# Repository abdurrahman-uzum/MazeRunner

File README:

A maze solving mini robot project conducted under Dokuz Eylül University Robot Topluluğu MazeRunner subgroup.

Project is uncomplete and discontinued.

Works present in this repository are my own works.

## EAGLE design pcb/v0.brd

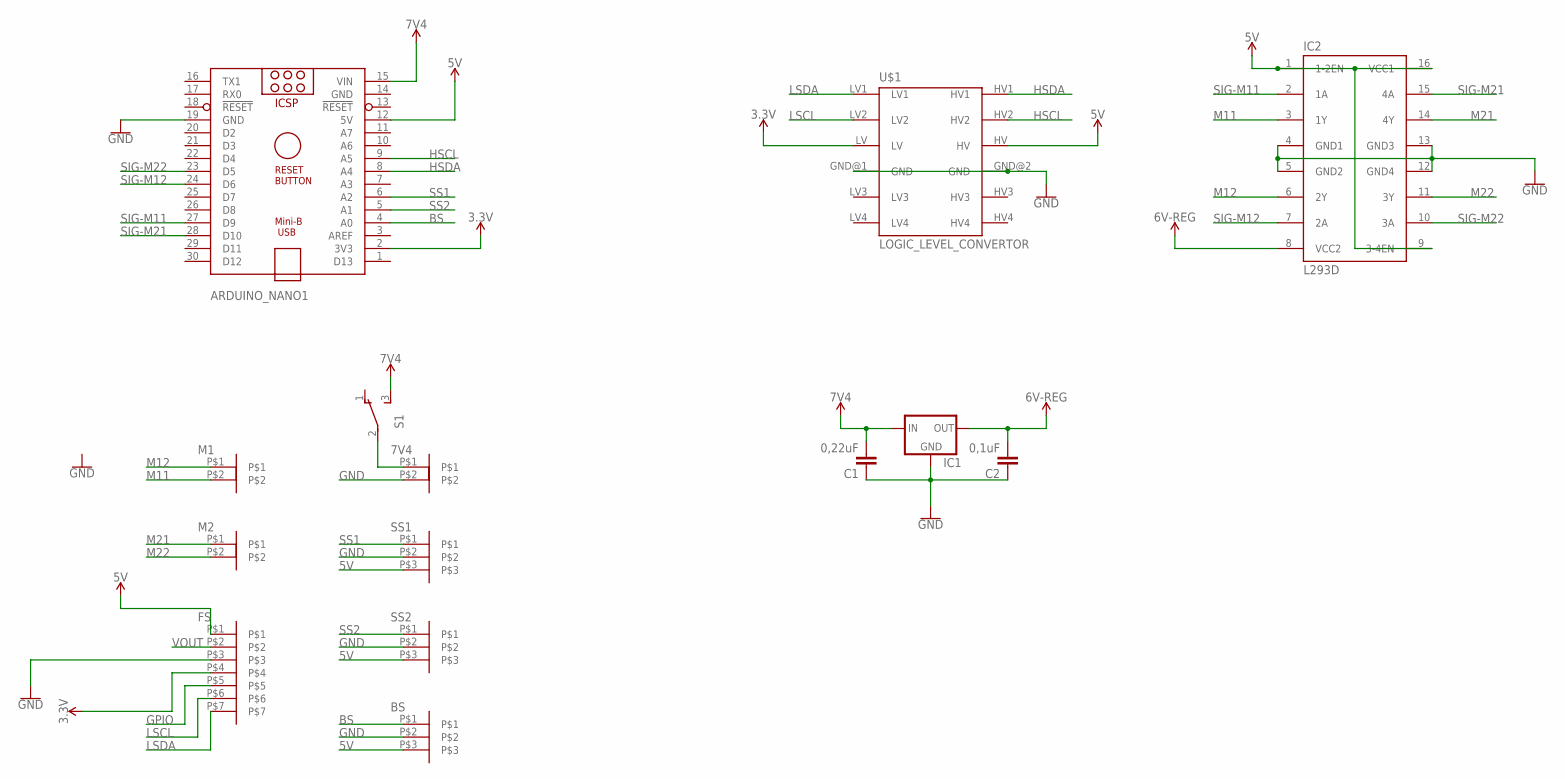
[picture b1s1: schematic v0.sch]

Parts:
7V4: 2MM_JST_2
ARDUINO_NANO1: ARDUINO_NANO
BS: 2MM_JST_3
C1: 0,22uF; C050-025X075
C2: 0,1uF; C050-025X075
FS: 2MM_JST_7
IC1: 78XXL
IC2: L293D; DIL16
M1, M2: 2MM_JST_2
S1: TL36PO; TL3XPO
SS1, SS2: 2MM_JST_3
U$1: LOGIC_LEVEL_CONVERTOR

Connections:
3.3V: ARDUINO_NANO1.2 (3V3), FS.P$4, U$1.LV
5V: ARDUINO_NANO1.12 (5V), BS.P$3, FS.P$1, IC2.1 (1-2EN), IC2.9 (3-4EN), IC2.16 (VCC1), SS1.P$3, SS2.P$3, U$1.HV
12V: C2.2, IC1.OUT, IC2.8 (VCC2)
BS: ARDUINO_NANO1.4 (A0), BS.P$1
GND: 7V4.P$2, ARDUINO_NANO1.14 (GND), ARDUINO_NANO1.19 (GND), BS.P$2, C1.1, C2.1, FS.P$3, IC1.GND, IC2.4 (GND1), IC2.5 (GND2), IC2.12 (GND4), IC2.13 (GND3), SS1.P$2, SS2.P$2, U$1.GND@1 (GND), U$1.GND@2 (GND)
GPIO: FS.P$5
HSCL: ARDUINO_NANO1.9 (A5), U$1.HV2
HSDA: ARDUINO_NANO1.8 (A4), U$1.HV1
LSCL: FS.P$6, U$1.LV2
LSDA: FS.P$7, U$1.LV1
M11: IC2.3 (1Y), M1.P$2
M12: IC2.6 (2Y), M1.P$1
M21: IC2.14 (4Y), M2.P$1
M22: IC2.11 (3Y), M2.P$2
unnamed: 7V4.P$1, S1.2
SIG-M11: ARDUINO_NANO1.27 (D9), IC2.2 (1A)
SIG-M12: ARDUINO_NANO1.24 (D6), IC2.7 (2A)
SIG-M21: ARDUINO_NANO1.28 (D10), IC2.15 (4A)
SIG-M22: ARDUINO_NANO1.23 (D5), IC2.10 (3A)
SS1: ARDUINO_NANO1.6 (A2), SS1.P$1
SS2: ARDUINO_NANO1.5 (A1), SS2.P$1
VCCIO: ARDUINO_NANO1.15 (VIN), C1.2, IC1.IN, S1.3 (S)
VOUT: FS.P$2

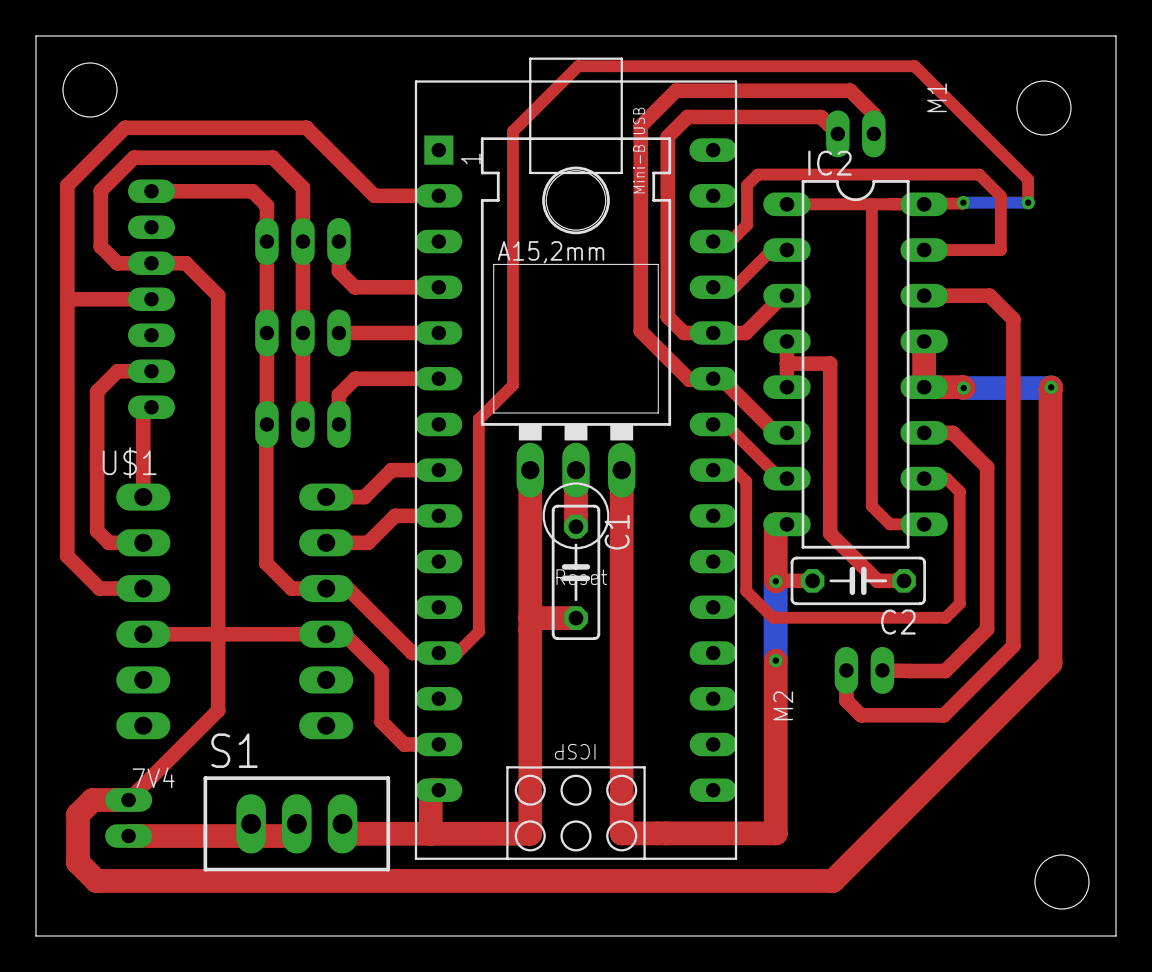
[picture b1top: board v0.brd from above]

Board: 2 copper layers, 60.0 x 50.0 mm, 14 parts (0 on the bottom side), 21 nets.

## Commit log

2022-05-16 Backup
2022-05-16 Explanation

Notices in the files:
parts and their libraries:
SparkFun-PowerSymbols: Licensing: Creative Commons ShareAlike 4.0 International - https://creativecommons.org/licenses/by-sa/4.0
